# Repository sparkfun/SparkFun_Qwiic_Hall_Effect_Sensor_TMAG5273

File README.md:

SparkFun Hall-Effect Sensor - TMAG5273
========================================

| [	SparkFun Linear 3D Hall-Effect Sensor - TMAG5273 (Qwiic)  *(SEN-23880)*](https://www.sparkfun.com/products/23880) | [SparkFun Mini Linear 3D Hall-Effect Sensor - TMAG5273 (Qwiic) *(SEN-23881)*](https://www.sparkfun.com/products/23881) |
| --- | --- |
|  |  |

Do you have a project that could use an inconspicuous [HID](https://en.wikipedia.org/wiki/Human_interface_device) (human interface device)? Ever wanted to tamper-proof your window alarm (i.e. contact sensors) from teenagers sneaking out or home intruders? Do you have a mechanical switch that keeps failing?

If you answered yes to any of those questions, the TMAG5273 from [Texas Instruments](https://www.ti.com) could be the solution to your problems. The TMAG5273 is low-power 3D [hall-effect sensor](https://en.wikipedia.org/wiki/Hall_effect_sensor) that is perfect for detecting and measuring changes in a nearby magnetic field. With a linear, magnetic range configurable to either ±40 mT or ±80 mT and TI's integrated angle calculation engine (CORDIC), the TMAG5273 can be used in various applications:

* Detecting motor movement
* Creating a [HID](https://en.wikipedia.org/wiki/Human_interface_device) (human interface device) *(i.e. joysticks, knobs, scroll wheels, etc.)*
* Replacing various mechanical switches (i.e. rotary encoders, contact switches, reed switches, etc.)*

In addition, the included magnetic tamper detection and wake-up/threshold settings can be configured to trigger interrupts through the I<sup>2</sup>C interface or only with the dedicated interrupt pin.

*These products are available in both the standard 1"x1" and mini Qwiic breakout boards. The mini is panel mount compatible for use in enclosures.*

Repository Contents
-------------------

* **[/docs](/docs/)** - Online documentation files
    * [assets](/docs/assets/) - Assets files
        * [board_files](/docs/assets/board_files/) - Files for the product design
            * [Eagle design files](/docs/assets/board_files/eagle_files.zip) (.zip)
            * [Schematic](/docs/assets/board_files/schematic.pdf) (.pdf)
            * [Dimensions](/docs/assets/board_files/dimensions.pdf) (.pdf)
        * [component_documentation](/docs/assets/component_documentation/) - Datasheets for hardware components
        * [img/hookup_guide/](/docs/assets/img/hookup_guide/) - Images for hookup guide documentation
* **[/Hardware](/Hardware/)** - Eagle design files (.brd, .sch)
  * **[/1U](/Hardware/1U/)** - 1"x1" Form Factor
    * **[/Production](/Hardware/1U/Production/)** - Production files
  * **[/Mini](/Hardware/Mini/)** - Mini Form Factor
    * **[/Production](/Hardware/Mini/Production/)** - Production files

Documentation
--------------

* **[Hookup Guide (mkdocs)](http://docs.sparkfun.com/SparkFun_Qwiic_Hall_Effect_Sensor_TMAG5273/)** - Hookup guide for the Qwiic hall-effect sensor hosted by GitHub pages.
  * [Arduino Library](https://github.com/sparkfun/SparkFun_TMAG5273_Arduino_Library/tree/main)

*Need to download or print our hookup guide?*

* [Print *(Print to PDF)* from Single-Page View](http://docs.sparkfun.com/SparkFun_Qwiic_Hall_Effect_Sensor_TMAG5273/print_view)

Product Variants
----------------

* [SEN-23880](https://www.sparkfun.com/products/23880)- v1.0, Initial Release *(1"x1" Form Factor)*
* [SEN-23881](https://www.sparkfun.com/products/23881)- v1.0, Initial Release *(Mini Form Factor)*

Version History
---------------

* [v10](https://github.com/sparkfun/SparkFun_Qwiic_Hall_Effect_Sensor_TMAG5273/releases/tag/v10) - Initial Release

License Information
-------------------

This product is ***open source***!

Please review the [`LICENSE.md`](./LICENSE.md) file for license information.

If you have any questions or concerns about licensing, please contact technical support on our [SparkFun forums](https://forum.sparkfun.com/viewforum.php?f=152).

Distributed as-is; no warranty is given.

- Your friends at SparkFun.

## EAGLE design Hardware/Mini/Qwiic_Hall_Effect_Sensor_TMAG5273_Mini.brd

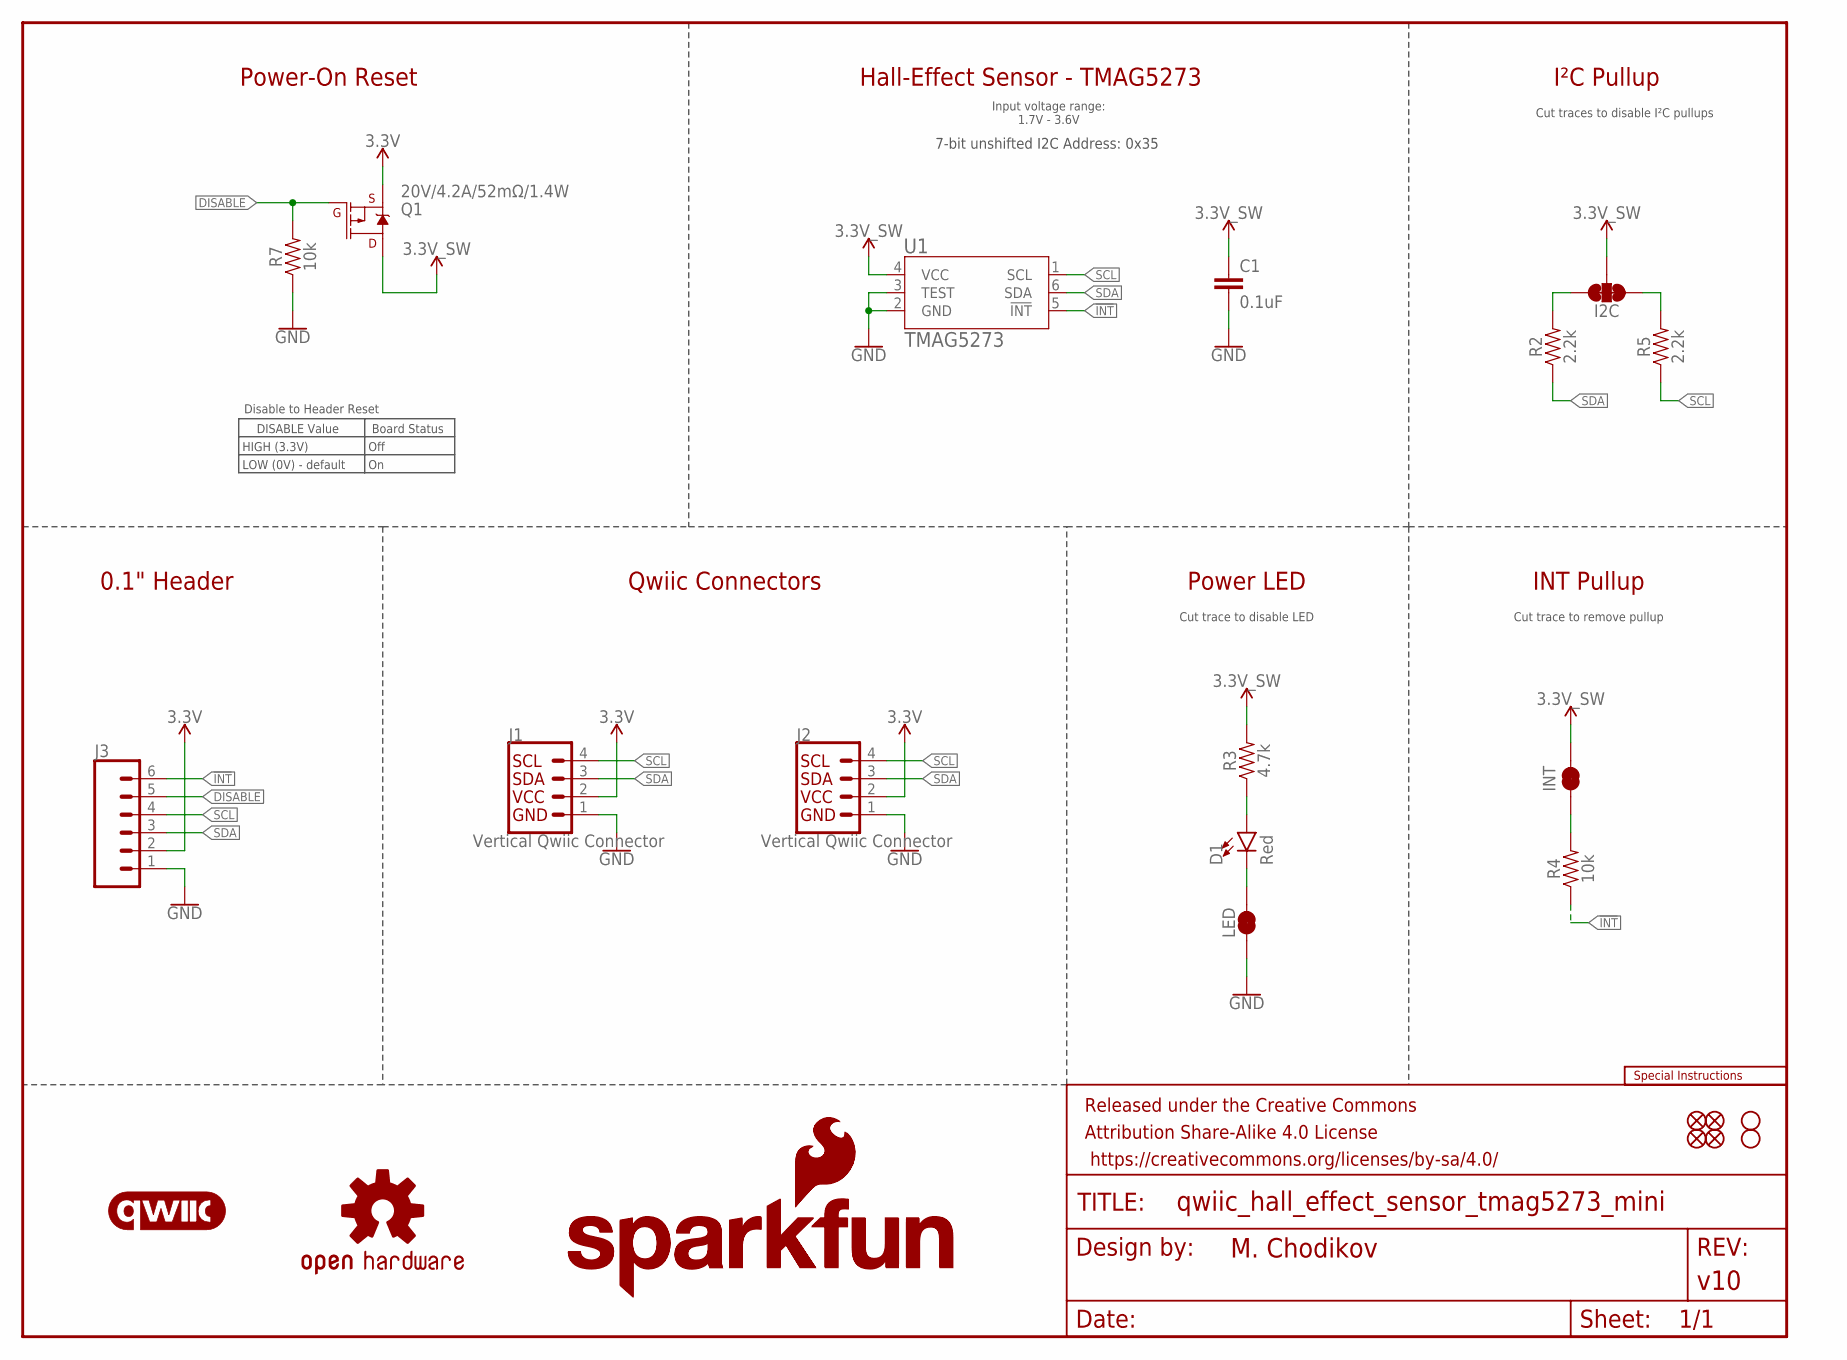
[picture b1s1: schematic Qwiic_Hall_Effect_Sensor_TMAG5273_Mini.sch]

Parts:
C1: 0.1uF; 0603
D1: Red; LED-0603
FD1, FD2, FD3, FD4: FIDUCIAL1X2; FIDUCIAL-1X2
FRAME1: FRAME-LETTER; CREATIVE_COMMONS
H2, H4: STAND-OFF
I2C: JUMPER-SMT_3_2-NC_TRACE_SILK; SMT-JUMPER_3_2-NC_TRACE_SILK
INT: JUMPER-SMT_2_NC_TRACE_SILK; SMT-JUMPER_2_NC_TRACE_SILK
J1, J2: Vertical Qwiic Connector; JST04_1MM_VERT
J3: CONN_06NO_SILK_FEMALE_PTH; 1X06_NO_SILK
LED: JUMPER-SMT_2_NC_TRACE_SILK; SMT-JUMPER_2_NC_TRACE_SILK
LOGO1: OSHW-LOGOMINI; OSHW-LOGO-MINI
LOGO2: SFE_LOGO_NAME_FLAME5_MM; SFE_LOGO_NAME_FLAME_5MM
LOGO3: QWIIC_LOGO_4MM; QWIIC_4MM
LOGO4: SFE_LOGO_NAME7_MM; SFE_LOGO_NAME_7MM
LOGO5: SPECIAL_INSTRUCTIONS-ORDERING; ORDERING_INSTRUCTIONS
LOGO6: SFE_LOGO_FLAME.1_INCH; SFE_LOGO_FLAME_.1
Q1: 20V/4.2A/52mΩ/1.4W; SOT23-3
R2, R5: 2.2k; 0603
R3: 4.7k; 0603
R4, R7: 10k; 0603
U1: TMAG5273; SOT23-6_DBV_TEX

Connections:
3.3V: J1.2, J2.2, J3.2, Q1.2 (S)
3.3V_SW: C1.1, I2C.2, INT.2, Q1.3 (D), R3.2, U1.4 (VCC)
!INT: J3.6, R4.1, U1.5 (!INT)
DISABLE: J3.5, Q1.1 (G), R7.2
GND: C1.2, J1.1, J2.1, J3.1, LED.1, R7.1, U1.2 (GND), U1.3 (TEST)
unnamed: D1.C, LED.2
unnamed: I2C.3, R2.2
unnamed: D1.A, R3.1
unnamed: INT.1, R4.2
unnamed: I2C.1, R5.2
SCL: J1.4, J2.4, J3.4, R5.1, U1.1 (SCL)
SDA: J1.3, J2.3, J3.3, R2.1, U1.6 (SDA)

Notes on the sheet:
7-bit unshifted I2C Address: 0x35
Hall-Effect Sensor - TMAG5273
I²C Pullup
Cut traces to disable I²C pullups
Input voltage range: 1.7V - 3.6V
Cut trace to disable LED
Power LED
Cut trace to remove pullup
INT Pullup
0.1" Header
Qwiic Connectors
Power-On Reset
Disable to Header Reset
DISABLE Value
HIGH (3.3V)
LOW (0V) - default
Off
Board Status

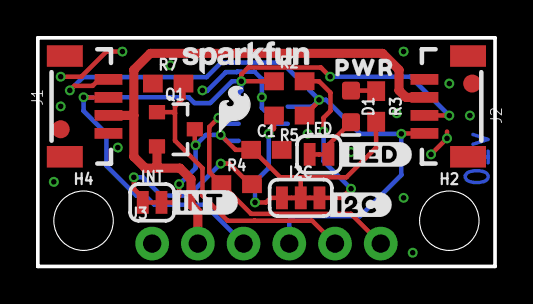
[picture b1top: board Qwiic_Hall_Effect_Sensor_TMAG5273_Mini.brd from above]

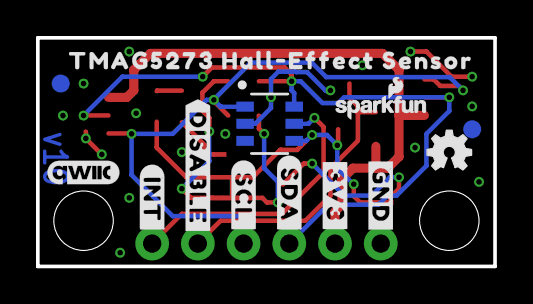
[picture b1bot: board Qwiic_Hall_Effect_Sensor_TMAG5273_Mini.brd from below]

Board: 2 copper layers, 25.4 x 12.7 mm, 39 parts (13 on the bottom side), 12 nets.

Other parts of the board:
U$1: PWR5282
U$2: #SCL#38
U$3: #SDA#37
U$4: #3V3#37
U$5: #GND#36
U$6: TMAG5273_HALL#EFFECT_SENSOR0
U$7: #DISABLE#5291
U$8: #I2C#5276
U$9: #INT#5285
U$10: #LED#5275
U$12: #INT#5287

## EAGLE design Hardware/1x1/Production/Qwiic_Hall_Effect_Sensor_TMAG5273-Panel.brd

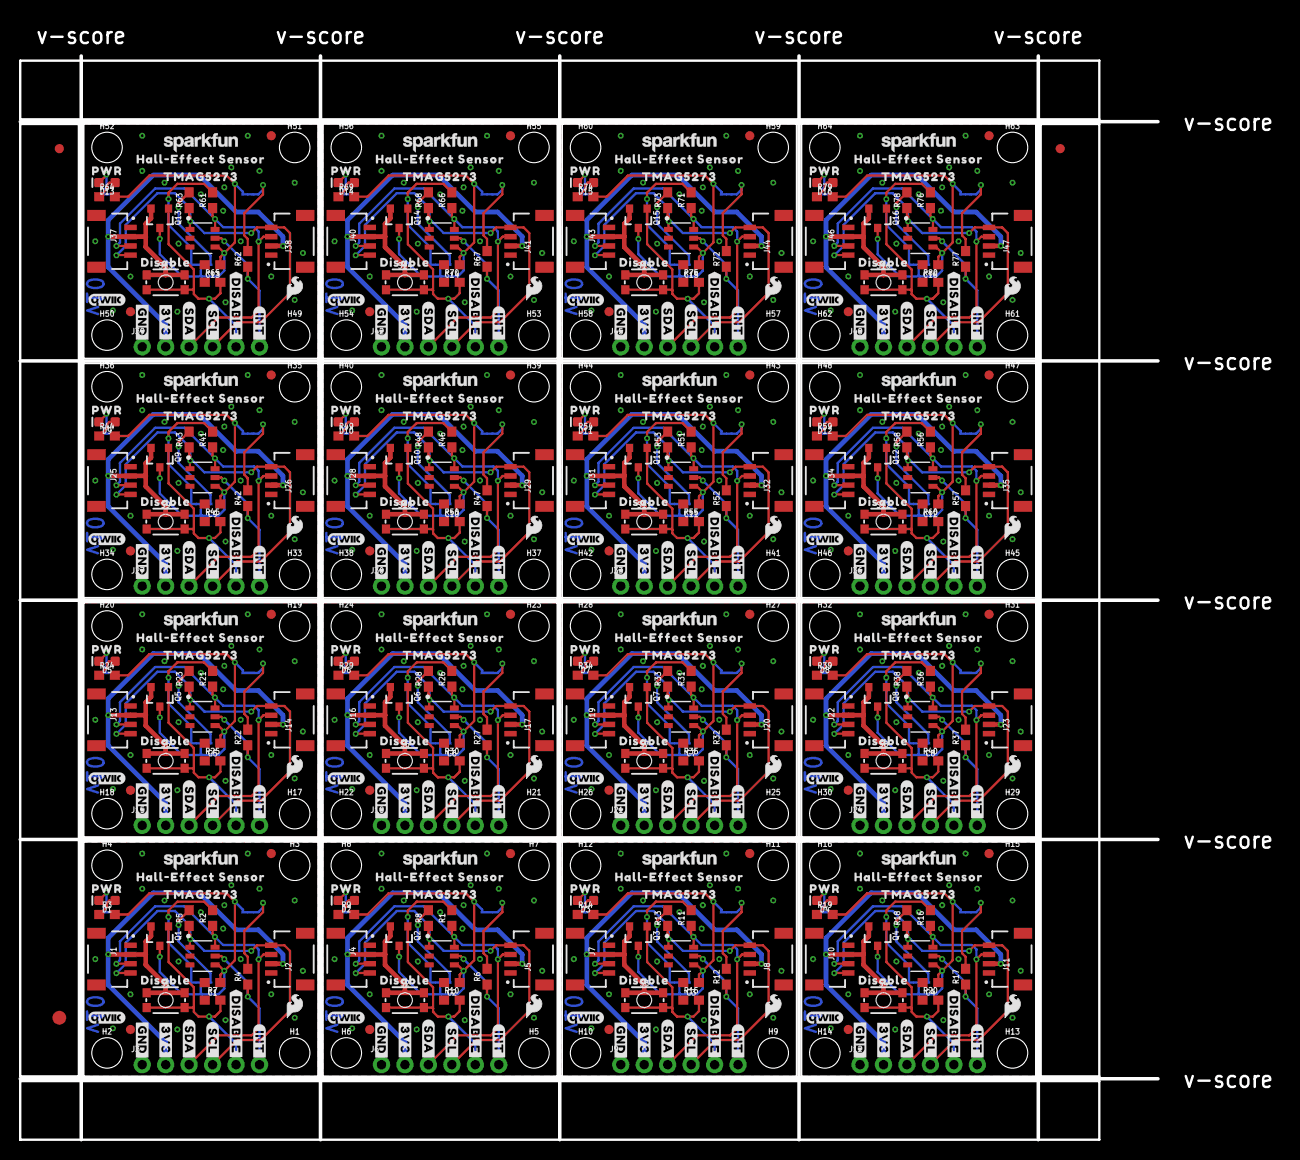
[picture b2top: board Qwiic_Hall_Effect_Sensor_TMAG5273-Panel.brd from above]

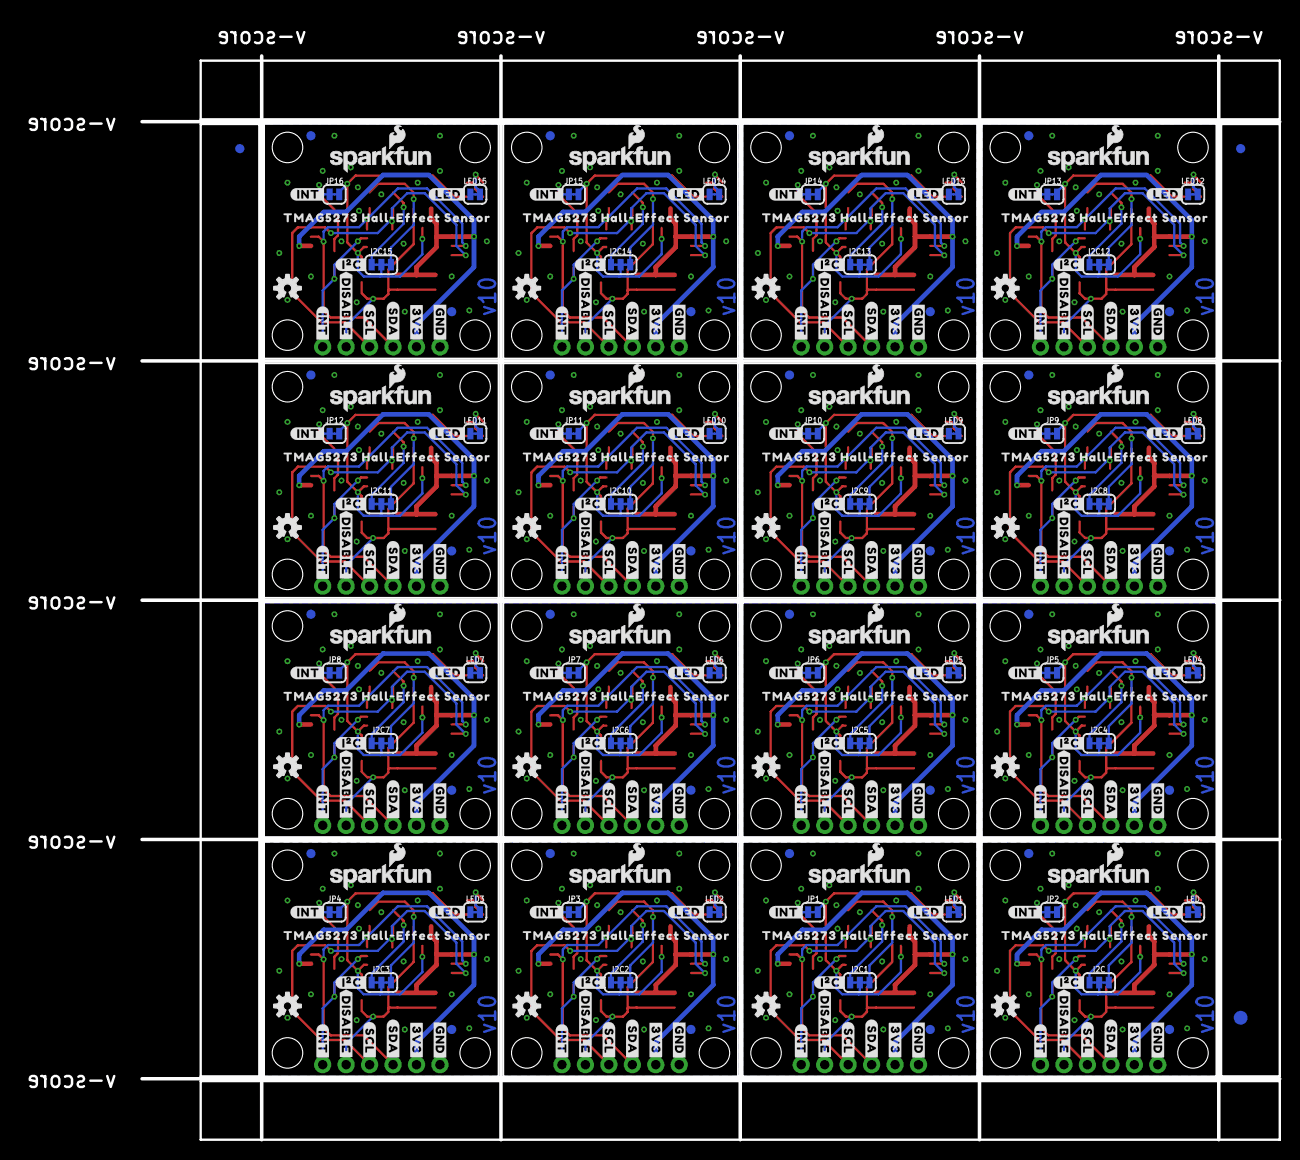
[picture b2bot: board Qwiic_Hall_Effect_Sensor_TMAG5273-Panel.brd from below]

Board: 2 copper layers, 136.4 x 121.2 mm, 790 parts (275 on the bottom side), 192 nets.

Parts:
C1, C2, C3, C4, C5, C6, C7, C8, C9, C10, C11, C12, C13, C14, C15, C16: 0.1uF; 0603
D1, D2, D3, D4, D5, D6, D7, D8, D9, D10, D11, D12, D13, D14, D15, D16: Red; LED-0603
E$1, E$2, E$3, E$4: FIDUCIAL-1X2
E$5, E$6: FIDUCIAL-1.5X3
FD1, FD2, FD3, FD4, FD5, FD6, FD7, FD8, FD9, FD10, FD11, FD12, FD13, FD14, FD15, FD16, FD17, FD18, FD19, FD20, FD21, FD22, FD23, FD24, FD25, FD26, FD27, FD28, FD29, FD30, FD31, FD32, FD33, FD34, FD35, FD36, FD37, FD38, FD39, FD40, FD41, FD42, FD43, FD44, FD45, FD46, FD47, FD48, FD49, FD50, FD51, FD52, FD53, FD54, FD55, FD56, FD57, FD58, FD59, FD60, FD61, FD62, FD63, FD64: FIDUCIAL1X2; FIDUCIAL-1X2
H1, H2, H3, H4, H5, H6, H7, H8, H9, H10, H11, H12, H13, H14, H15, H16, H17, H18, H19, H20, H21, H22, H23, H24, H25, H26, H27, H28, H29, H30, H31, H32, H33, H34, H35, H36, H37, H38, H39, H40, H41, H42, H43, H44, H45, H46, H47, H48, H49, H50, H51, H52, H53, H54, H55, H56, H57, H58, H59, H60, H61, H62, H63, H64: STAND-OFF
I2C, I2C1, I2C2, I2C3, I2C4, I2C5, I2C6, I2C7, I2C8, I2C9, I2C10, I2C11, I2C12, I2C13, I2C14, I2C15: JUMPER-SMT_3_2-NC_TRACE_SILK; SMT-JUMPER_3_2-NC_TRACE_SILK
J1, J2, J4, J5, J7, J8, J10, J11, J13, J14, J16, J17, J19, J20, J22, J23, J25, J26, J28, J29, J31, J32, J34, J35, J37, J38, J40, J41, J43, J44, J46, J47: QWIIC_RIGHT_ANGLE; JST04_1MM_RA
J3, J6, J9, J12, J15, J18, J21, J24, J27, J30, J33, J36, J39, J42, J45, J48: 1X06_NO_SILK
JP1, JP2, JP3, JP4, JP5, JP6, JP7, JP8, JP9, JP10, JP11, JP12, JP13, JP14, JP15, JP16: JUMPER-SMT_2_NC_TRACE_SILK; SMT-JUMPER_2_NC_TRACE_SILK
LED, LED1, LED2, LED3, LED4, LED5, LED6, LED7, LED8, LED9, LED10, LED11, LED12, LED13, LED14, LED15: JUMPER-SMT_2_NC_TRACE_SILK; SMT-JUMPER_2_NC_TRACE_SILK
LOGO1, LOGO5, LOGO11, LOGO16, LOGO21, LOGO26, LOGO31, LOGO36, LOGO41, LOGO46, LOGO51, LOGO56, LOGO61, LOGO66, LOGO71, LOGO76: OSHW-LOGOS; OSHW-LOGO-S
LOGO2, LOGO7, LOGO12, LOGO17, LOGO22, LOGO27, LOGO32, LOGO37, LOGO42, LOGO47, LOGO52, LOGO57, LOGO62, LOGO67, LOGO72, LOGO77: SFE_LOGO_NAME_FLAME.1_INCH; SFE_LOGO_NAME_FLAME_.1
LOGO3, LOGO8, LOGO13, LOGO18, LOGO23, LOGO28, LOGO33, LOGO38, LOGO43, LOGO48, LOGO53, LOGO58, LOGO63, LOGO68, LOGO73, LOGO78: QWIIC_LOGO_4MM; QWIIC_4MM
LOGO4, LOGO9, LOGO14, LOGO19, LOGO24, LOGO29, LOGO34, LOGO39, LOGO44, LOGO49, LOGO54, LOGO59, LOGO64, LOGO69, LOGO74, LOGO79: SFE_LOGO_NAME8_MM; SFE_LOGO_NAME_8MM
LOGO6, LOGO10, LOGO15, LOGO20, LOGO25, LOGO30, LOGO35, LOGO40, LOGO45, LOGO50, LOGO55, LOGO60, LOGO65, LOGO70, LOGO75, LOGO80: SFE_LOGO_FLAME.1_INCH; SFE_LOGO_FLAME_.1
Q1, Q2, Q3, Q4, Q5, Q6, Q7, Q8, Q9, Q10, Q11, Q12, Q13, Q14, Q15, Q16: 20V/4.2A/52mΩ/1.4W; SOT23-3
R1, R2, R5, R8, R11, R13, R16, R18, R21, R23, R26, R28, R31, R33, R36, R38, R41, R43, R46, R48, R51, R53, R56, R58, R61, R63, R66, R68, R71, R73, R76, R78: 2.2k; 0603
R3, R9, R14, R19, R24, R29, R34, R39, R44, R49, R54, R59, R64, R69, R74, R79: 4.7k; 0603
R4, R6, R7, R10, R12, R15, R17, R20, R22, R25, R27, R30, R32, R35, R37, R40, R42, R45, R47, R50, R52, R55, R57, R60, R62, R65, R67, R70, R72, R75, R77, R80: 10k; 0603
S1, S2, S3, S4, S5, S6, S7, S8, S9, S10, S11, S12, S13, S14, S15, S16: TACTILE_SWITCH_SMD_4.6X2.8MM
U1, U2, U3, U4, U5, U6, U7, U8, U9, U10, U11, U12, U13, U14, U15, U16: TMAG5273; SOT23-6_DBV_TEX
U$1, U$22, U$42, U$62, U$82, U$102, U$122, U$142, U$162, U$182, U$202, U$222, U$242, U$262, U$282, U$302: #3V3#37
U$2, U$21, U$41, U$61, U$81, U$101, U$121, U$141, U$161, U$181, U$201, U$221, U$241, U$261, U$281, U$301: #GND#36
U$3, U$23, U$43, U$63, U$83, U$103, U$123, U$143, U$163, U$183, U$203, U$223, U$243, U$263, U$283, U$303: #SDA#37
U$4, U$24, U$44, U$64, U$84, U$104, U$124, U$144, U$164, U$184, U$204, U$224, U$244, U$264, U$284, U$304: #SCL#38
U$5, U$17, U$36, U$37, U$56, U$57, U$76, U$77, U$96, U$97, U$116, U$117, U$136, U$137, U$156, U$157, U$176, U$177, U$196, U$197, U$216, U$217, U$236, U$237, U$256, U$257, U$276, U$277, U$296, U$297, U$316, U$317: #INT#5285
U$6, U$38, U$58, U$78, U$98, U$118, U$138, U$158, U$178, U$198, U$218, U$238, U$258, U$278, U$298, U$318: #INT#5289
U$7, U$25, U$45, U$65, U$85, U$105, U$125, U$145, U$165, U$185, U$205, U$225, U$245, U$265, U$285, U$305: PWR41
U$8, U$26, U$46, U$66, U$86, U$106, U$126, U$146, U$166, U$186, U$206, U$226, U$246, U$266, U$286, U$306: #LED#42
U$9, U$15, U$39, U$40, U$59, U$60, U$79, U$80, U$99, U$100, U$119, U$120, U$139, U$140, U$159, U$160, U$179, U$180, U$199, U$200, U$219, U$220, U$239, U$240, U$259, U$260, U$279, U$280, U$299, U$300, U$319, U$320: #DISABLE#5290
U$10, U$27, U$47, U$67, U$87, U$107, U$127, U$147, U$167, U$187, U$207, U$227, U$247, U$267, U$287, U$307: #I�C#0
U$11, U$28, U$48, U$68, U$88, U$108, U$128, U$148, U$168, U$188, U$208, U$228, U$248, U$268, U$288, U$308: HALL#EFFECT_SENSOR45
U$12, U$29, U$49, U$69, U$89, U$109, U$129, U$149, U$169, U$189, U$209, U$229, U$249, U$269, U$289, U$309: TMAG527346
U$13, U$35, U$55, U$75, U$95, U$115, U$135, U$155, U$175, U$195, U$215, U$235, U$255, U$275, U$295, U$315: DISABLE5281
U$14, U$30, U$50, U$70, U$90, U$110, U$130, U$150, U$170, U$190, U$210, U$230, U$250, U$270, U$290, U$310: #SDA#5280
U$16, U$31, U$51, U$71, U$91, U$111, U$131, U$151, U$171, U$191, U$211, U$231, U$251, U$271, U$291, U$311: #SCL#5281
U$18, U$32, U$52, U$72, U$92, U$112, U$132, U$152, U$172, U$192, U$212, U$232, U$252, U$272, U$292, U$312: #3V3#0
U$19, U$33, U$53, U$73, U$93, U$113, U$133, U$153, U$173, U$193, U$213, U$233, U$253, U$273, U$293, U$313: #GND#4
U$20, U$34, U$54, U$74, U$94, U$114, U$134, U$154, U$174, U$194, U$214, U$234, U$254, U$274, U$294, U$314: TMAG5273_HALL#EFFECT_SENSOR5

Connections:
3.3V: J1.2, J2.2, J3.2, Q1.2, S1.3, S1.4
3.3V1: J4.2, J5.2, J6.2, Q2.2, S2.3, S2.4
3.3V2: J7.2, J8.2, J9.2, Q3.2, S3.3, S3.4
3.3V3: J10.2, J11.2, J12.2, Q4.2, S4.3, S4.4
3.3V4: J13.2, J14.2, J15.2, Q5.2, S5.3, S5.4
3.3V5: J16.2, J17.2, J18.2, Q6.2, S6.3, S6.4
3.3V6: J19.2, J20.2, J21.2, Q7.2, S7.3, S7.4
3.3V7: J22.2, J23.2, J24.2, Q8.2, S8.3, S8.4
3.3V8: J25.2, J26.2, J27.2, Q9.2, S9.3, S9.4
3.3V9: J28.2, J29.2, J30.2, Q10.2, S10.3, S10.4
3.3V10: J31.2, J32.2, J33.2, Q11.2, S11.3, S11.4
3.3V11: J34.2, J35.2, J36.2, Q12.2, S12.3, S12.4
3.3V12: J37.2, J38.2, J39.2, Q13.2, S13.3, S13.4
3.3V13: J40.2, J41.2, J42.2, Q14.2, S14.3, S14.4
3.3V14: J43.2, J44.2, J45.2, Q15.2, S15.3, S15.4
3.3V15: J46.2, J47.2, J48.2, Q16.2, S16.3, S16.4
3.3V_SW: C1.1, I2C.2, JP2.2, Q1.3, R3.2, U1.4
3.3V_SW1: C2.1, I2C1.2, JP1.2, Q2.3, R9.2, U2.4
3.3V_SW2: C3.1, I2C2.2, JP3.2, Q3.3, R14.2, U3.4
3.3V_SW3: C4.1, I2C3.2, JP4.2, Q4.3, R19.2, U4.4
3.3V_SW4: C5.1, I2C4.2, JP5.2, Q5.3, R24.2, U5.4
3.3V_SW5: C6.1, I2C5.2, JP6.2, Q6.3, R29.2, U6.4
3.3V_SW6: C7.1, I2C6.2, JP7.2, Q7.3, R34.2, U7.4
3.3V_SW7: C8.1, I2C7.2, JP8.2, Q8.3, R39.2, U8.4
3.3V_SW8: C9.1, I2C8.2, JP9.2, Q9.3, R44.2, U9.4
3.3V_SW9: C10.1, I2C9.2, JP10.2, Q10.3, R49.2, U10.4
3.3V_SW10: C11.1, I2C10.2, JP11.2, Q11.3, R54.2, U11.4
3.3V_SW11: C12.1, I2C11.2, JP12.2, Q12.3, R59.2, U12.4
3.3V_SW12: C13.1, I2C12.2, JP13.2, Q13.3, R64.2, U13.4
3.3V_SW13: C14.1, I2C13.2, JP14.2, Q14.3, R69.2, U14.4
3.3V_SW14: C15.1, I2C14.2, JP15.2, Q15.3, R74.2, U15.4
3.3V_SW15: C16.1, I2C15.2, JP16.2, Q16.3, R79.2, U16.4
!INT: J3.6, R4.1, U1.5
!INT1: J6.6, R6.1, U2.5
!INT2: J9.6, R12.1, U3.5
!INT3: J12.6, R17.1, U4.5
!INT4: J15.6, R22.1, U5.5
!INT5: J18.6, R27.1, U6.5
!INT6: J21.6, R32.1, U7.5
!INT7: J24.6, R37.1, U8.5
!INT8: J27.6, R42.1, U9.5
!INT9: J30.6, R47.1, U10.5
!INT10: J33.6, R52.1, U11.5
!INT11: J36.6, R57.1, U12.5
!INT12: J39.6, R62.1, U13.5
!INT13: J42.6, R67.1, U14.5
!INT14: J45.6, R72.1, U15.5
!INT15: J48.6, R77.1, U16.5
DISABLE: J3.5, Q1.1, R7.2, S1.1, S1.2
DISABLE1: J6.5, Q2.1, R10.2, S2.1, S2.2
DISABLE2: J9.5, Q3.1, R15.2, S3.1, S3.2
DISABLE3: J12.5, Q4.1, R20.2, S4.1, S4.2
DISABLE4: J15.5, Q5.1, R25.2, S5.1, S5.2
DISABLE5: J18.5, Q6.1, R30.2, S6.1, S6.2
DISABLE6: J21.5, Q7.1, R35.2, S7.1, S7.2
DISABLE7: J24.5, Q8.1, R40.2, S8.1, S8.2
DISABLE8: J27.5, Q9.1, R45.2, S9.1, S9.2
DISABLE9: J30.5, Q10.1, R50.2, S10.1, S10.2
DISABLE10: J33.5, Q11.1, R55.2, S11.1, S11.2
DISABLE11: J36.5, Q12.1, R60.2, S12.1, S12.2
DISABLE12: J39.5, Q13.1, R65.2, S13.1, S13.2
DISABLE13: J42.5, Q14.1, R70.2, S14.1, S14.2
DISABLE14: J45.5, Q15.1, R75.2, S15.1, S15.2
DISABLE15: J48.5, Q16.1, R80.2, S16.1, S16.2
GND: C1.2, J1.1, J2.1, J3.1, LED.1, R7.1, U1.2, U1.3
GND1: C2.2, J4.1, J5.1, J6.1, LED1.1, R10.1, U2.2, U2.3
GND2: C3.2, J7.1, J8.1, J9.1, LED2.1, R15.1, U3.2, U3.3
GND3: C4.2, J10.1, J11.1, J12.1, LED3.1, R20.1, U4.2, U4.3
GND4: C5.2, J13.1, J14.1, J15.1, LED4.1, R25.1, U5.2, U5.3
GND5: C6.2, J16.1, J17.1, J18.1, LED5.1, R30.1, U6.2, U6.3
GND6: C7.2, J19.1, J20.1, J21.1, LED6.1, R35.1, U7.2, U7.3
GND7: C8.2, J22.1, J23.1, J24.1, LED7.1, R40.1, U8.2, U8.3
GND8: C9.2, J25.1, J26.1, J27.1, LED8.1, R45.1, U9.2, U9.3
GND9: C10.2, J28.1, J29.1, J30.1, LED9.1, R50.1, U10.2, U10.3
GND10: C11.2, J31.1, J32.1, J33.1, LED10.1, R55.1, U11.2, U11.3
GND11: C12.2, J34.1, J35.1, J36.1, LED11.1, R60.1, U12.2, U12.3
GND12: C13.2, J37.1, J38.1, J39.1, LED12.1, R65.1, U13.2, U13.3
GND13: C14.2, J40.1, J41.1, J42.1, LED13.1, R70.1, U14.2, U14.3
GND14: C15.2, J43.1, J44.1, J45.1, LED14.1, R75.1, U15.2, U15.3
GND15: C16.2, J46.1, J47.1, J48.1, LED15.1, R80.1, U16.2, U16.3
unnamed: D1.C, LED.2
unnamed: I2C.3, R2.2
unnamed: D2.A, R9.1
unnamed: D1.A, R3.1
unnamed: JP2.1, R4.2
unnamed: I2C.1, R5.2
unnamed: D2.C, LED1.2
unnamed: JP1.1, R6.2
unnamed: I2C1.3, R1.2
unnamed: I2C1.1, R8.2
unnamed: D3.A, R14.1
unnamed: D3.C, LED2.2
unnamed: JP3.1, R12.2
unnamed: I2C2.3, R11.2
unnamed: I2C2.1, R13.2
unnamed: D4.A, R19.1
unnamed: D4.C, LED3.2
unnamed: JP4.1, R17.2
unnamed: I2C3.3, R16.2
unnamed: I2C3.1, R18.2
unnamed: D5.A, R24.1
unnamed: D5.C, LED4.2
unnamed: JP5.1, R22.2
unnamed: I2C4.3, R21.2
unnamed: I2C4.1, R23.2
unnamed: D6.A, R29.1
unnamed: D6.C, LED5.2
unnamed: JP6.1, R27.2
unnamed: I2C5.3, R26.2
unnamed: I2C5.1, R28.2
unnamed: D7.A, R34.1
unnamed: D7.C, LED6.2
unnamed: JP7.1, R32.2
unnamed: I2C6.3, R31.2
unnamed: I2C6.1, R33.2
unnamed: D8.A, R39.1
unnamed: D8.C, LED7.2
unnamed: JP8.1, R37.2
unnamed: I2C7.3, R36.2
unnamed: I2C7.1, R38.2
unnamed: D9.A, R44.1
unnamed: D9.C, LED8.2
unnamed: JP9.1, R42.2
unnamed: I2C8.3, R41.2
unnamed: I2C8.1, R43.2
unnamed: D10.A, R49.1
unnamed: D10.C, LED9.2
unnamed: JP10.1, R47.2
unnamed: I2C9.3, R46.2
unnamed: I2C9.1, R48.2
unnamed: D11.A, R54.1
unnamed: D11.C, LED10.2
unnamed: JP11.1, R52.2
unnamed: I2C10.3, R51.2
unnamed: I2C10.1, R53.2
unnamed: D12.A, R59.1
unnamed: D12.C, LED11.2
unnamed: JP12.1, R57.2
unnamed: I2C11.3, R56.2
unnamed: I2C11.1, R58.2
unnamed: D13.A, R64.1
unnamed: D13.C, LED12.2
unnamed: JP13.1, R62.2
unnamed: I2C12.3, R61.2
unnamed: I2C12.1, R63.2
unnamed: D14.A, R69.1
unnamed: D14.C, LED13.2
unnamed: JP14.1, R67.2
unnamed: I2C13.3, R66.2
unnamed: I2C13.1, R68.2
unnamed: D15.A, R74.1
unnamed: D15.C, LED14.2
unnamed: JP15.1, R72.2
unnamed: I2C14.3, R71.2
unnamed: I2C14.1, R73.2
unnamed: D16.A, R79.1
unnamed: D16.C, LED15.2
unnamed: JP16.1, R77.2
unnamed: I2C15.3, R76.2
unnamed: I2C15.1, R78.2
SCL: J1.4, J2.4, J3.4, R5.1, U1.1
SCL1: J4.4, J5.4, J6.4, R8.1, U2.1
SCL2: J7.4, J8.4, J9.4, R13.1, U3.1
SCL3: J10.4, J11.4, J12.4, R18.1, U4.1
SCL4: J13.4, J14.4, J15.4, R23.1, U5.1
SCL5: J16.4, J17.4, J18.4, R28.1, U6.1
SCL6: J19.4, J20.4, J21.4, R33.1, U7.1
SCL7: J22.4, J23.4, J24.4, R38.1, U8.1
SCL8: J25.4, J26.4, J27.4, R43.1, U9.1
SCL9: J28.4, J29.4, J30.4, R48.1, U10.1
SCL10: J31.4, J32.4, J33.4, R53.1, U11.1
SCL11: J34.4, J35.4, J36.4, R58.1, U12.1
SCL12: J37.4, J38.4, J39.4, R63.1, U13.1
SCL13: J40.4, J41.4, J42.4, R68.1, U14.1
SCL14: J43.4, J44.4, J45.4, R73.1, U15.1
SCL15: J46.4, J47.4, J48.4, R78.1, U16.1
SDA: J1.3, J2.3, J3.3, R2.1, U1.6
SDA1: J4.3, J5.3, J6.3, R1.1, U2.6
SDA2: J7.3, J8.3, J9.3, R11.1, U3.6
SDA3: J10.3, J11.3, J12.3, R16.1, U4.6
SDA4: J13.3, J14.3, J15.3, R21.1, U5.6
SDA5: J16.3, J17.3, J18.3, R26.1, U6.6
SDA6: J19.3, J20.3, J21.3, R31.1, U7.6
SDA7: J22.3, J23.3, J24.3, R36.1, U8.6
SDA8: J25.3, J26.3, J27.3, R41.1, U9.6
SDA9: J28.3, J29.3, J30.3, R46.1, U10.6
SDA10: J31.3, J32.3, J33.3, R51.1, U11.6
SDA11: J34.3, J35.3, J36.3, R56.1, U12.6
SDA12: J37.3, J38.3, J39.3, R61.1, U13.6
SDA13: J40.3, J41.3, J42.3, R66.1, U14.6
SDA14: J43.3, J44.3, J45.3, R71.1, U15.6
SDA15: J46.3, J47.3, J48.3, R76.1, U16.6

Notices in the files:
parts and their libraries:
SparkFun-Aesthetics: Licensing: Creative Commons ShareAlike 4.0 International - https://creativecommons.org/licenses/by-sa/4.0
SparkFun-Aesthetics: Released under the Creative Commons Attribution Share-Alike 4.0 License
SparkFun-Aesthetics: https://creativecommons.org/licenses/by-sa/4.0
